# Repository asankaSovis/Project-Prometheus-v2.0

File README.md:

# 🔥 Project Prometheus v2.0

---

💸 Please consider donating on [Paypal](https://www.paypal.com/donate/?hosted_button_id=4EWXTWQ9FUFLA) to keep this project alive.

**Prometheus Fire Alarm System** is a fire alarm system and an extinguishing system that allows real-time monitoring via software. It can perform smart extinguishing on-site while simultaneously providing connectivity to multiple devices via the control panel. Prometheus is designed to be as simple and resilient as possible while making it safe to use and operate within a household.

**Prometheus 2.0** is the next generation of [Prometheus Fire Alarm System](https://github.com/asankaSovis/prometheus-fire-alarm); the future of household safety and monitoring. Developed on the nRF7002 platform, it brings all the features of v1.0 to the nRF platform along with additional features made possible by the nRF platform.

> 
> 3D view of the enclosure design

## 📜 License
> Project Prometheus v2.0 is licensed under the **GNU General Public License v3.0**.

Permissions of this strong copyleft license are conditioned on making available complete source code of licensed works and modifications, which include larger works using a licensed work, under the same license. Copyright and license notices must be preserved. Contributors provide an express grant of patent rights.

### Permissions
✔️ Commercial use | Modification | Distribution | Patent use | Private use

### Limitations
❌ Liability | Warranty

### Conditions
ℹ️ License and copyright notice | State changes | Disclose source | Same license 

Refer to the [License declaration](./LICENSE) for more details.

## 💾 Documentation
Please refer to the following links for different sections of documentation.

1. [Preface](./Documentation/Preface.md)
2. [Introduction](./Documentation/Introduction.md)
3. [Technical Specification](./Documentation/Technical_Specifications.md)
4. [Hardware Specification](./Documentation/Hardware_Specifications.md)
5. [Software Specification](./Documentation/Software_Specifications.md)
6. [Operational Details](./Documentation/Operational_Details.md)
7. [Project Management](./Documentation/Project_Management.md)
8. [Bill of Material](./Documentation/Bill_of_Material.md)
9. [References](./Documentation/References.md)
10. [Conclusion](./Documentation/Conclusion.md)

## 📊 Demonstration

> 
> Demonstration video of the final product

`© 2024 Asanka Sovis`

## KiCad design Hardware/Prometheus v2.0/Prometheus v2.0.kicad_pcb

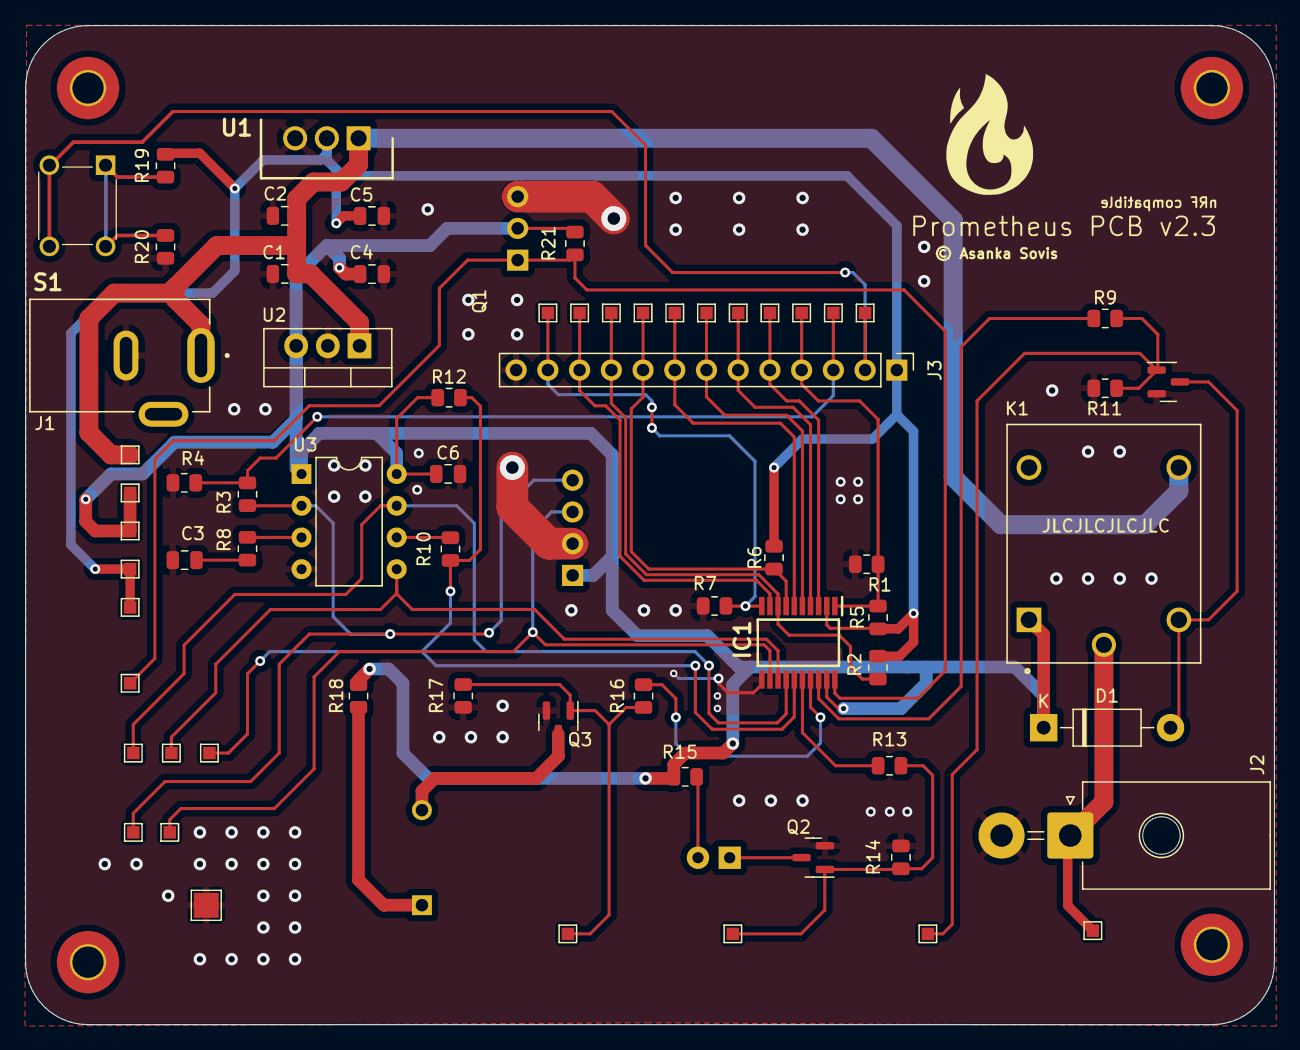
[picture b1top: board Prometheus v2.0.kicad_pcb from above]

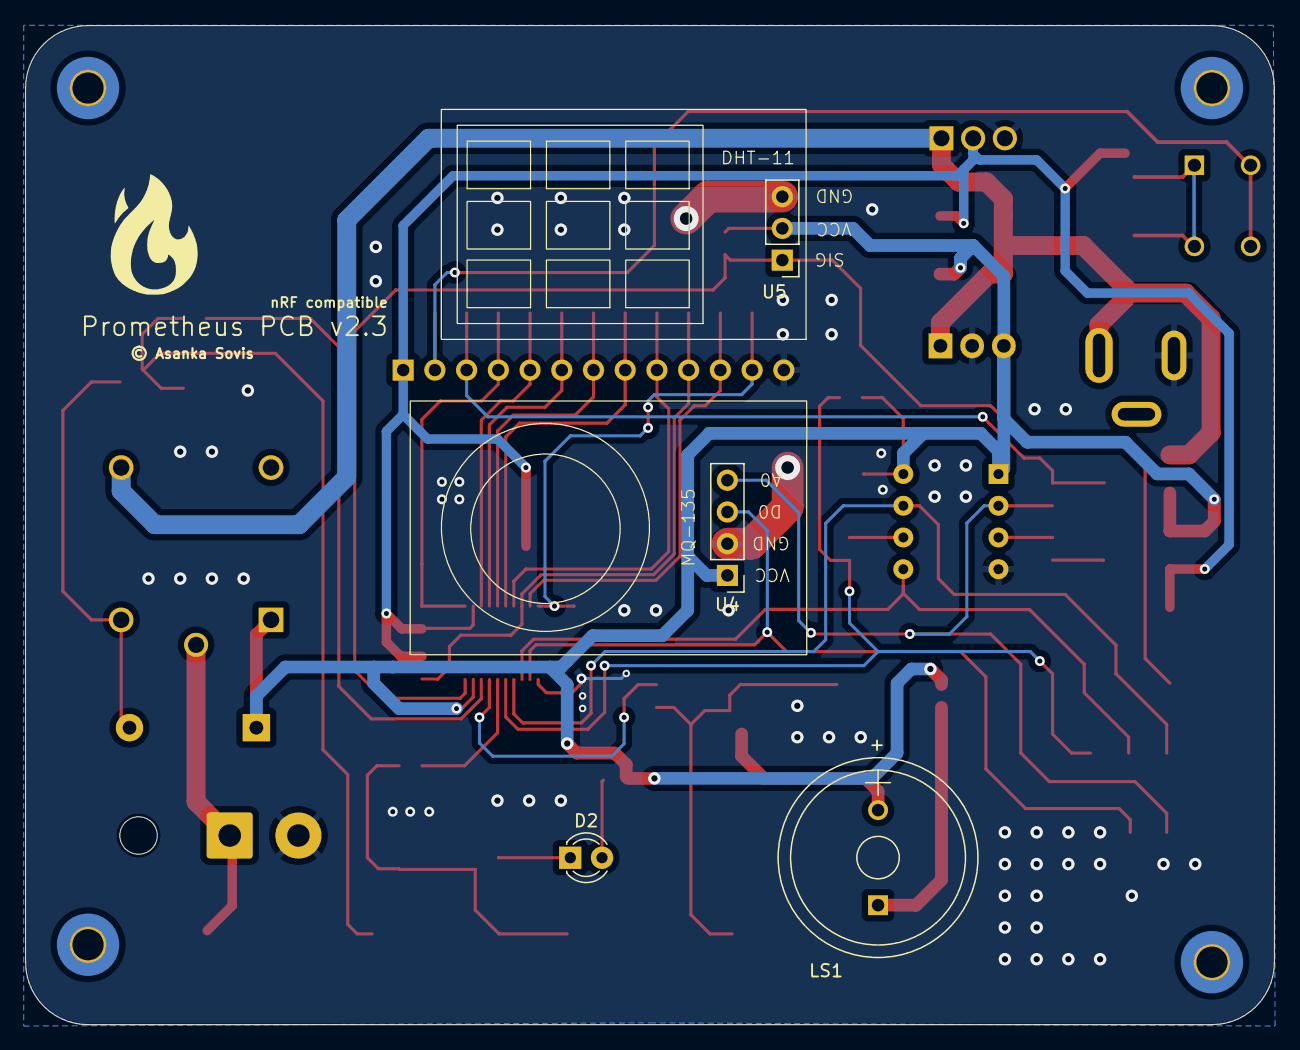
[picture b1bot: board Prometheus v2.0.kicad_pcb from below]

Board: 2 copper layers, 100.0 x 80.0 mm, 75 parts (4 on the bottom side), 37 nets.

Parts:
C1, C2, C4, C5: 10uF; C_0805_2012Metric
C3, C6: 0.1uF; C_0805_2012Metric
D1: 1N4001; D_DO-41_SOD81_P10.16mm_Horizontal
D2: LED; LED_D3.0mm_FlatTop
H1, H2, H3, H4: MountingHole; MountingHole_2.5mm_Pad_TopBottom
IC1: TXS0108EQPWRQ1; SOP65P640X120-20N
J1: DC-005-5A-2.0; XKB_DC-005-5A-2.0
J2: Conn_01x02_Socket; Molex_Mega-Fit_76825-0002_2x01_P5.70mm_Horizontal
J3: Conn_01x13_Pin; PinHeader_1x13_P2.54mm_Vertical
K1: SRD-05VDC-SL-C; RELAY_SRD-05VDC-SL-C
LS1: CPE-222H; MagneticBuzzer_StarMicronics_HMB-06_HMB-12
Q1, Q2, Q3: IRLML6246; SOT-23
R1, R2, R5, R6, R20: DNP; R_0805_2012Metric
R3, R7, R11, R12, R14, R17, R21: 10k; R_0805_2012Metric
R4: 20k; R_0805_2012Metric
R8: 2k; R_0805_2012Metric
R9, R10, R13, R16, R19: 100R; R_0805_2012Metric
R15, R18: 220R; R_0805_2012Metric
S1: DTS-62N-V; DTS62NV
TP1: 12V_TP; TestPoint_Pad_1.0x1.0mm
TP2: MQ_135_A_3V3_TP; TestPoint_Pad_1.0x1.0mm
TP3: VREF_A_TP; TestPoint_Pad_1.0x1.0mm
TP4: 5V_TP; TestPoint_Pad_1.0x1.0mm
TP5: 3V3_TP; TestPoint_Pad_1.0x1.0mm
TP6: LS_EN_TP; TestPoint_Pad_1.0x1.0mm
TP7: MQ_135_SCL_TP; TestPoint_Pad_1.0x1.0mm
TP8: MQ_135_CS_TP; TestPoint_Pad_1.0x1.0mm
TP9: VREF_B_TP; TestPoint_Pad_1.0x1.0mm
TP10: Solenoid_In_TP; TestPoint_Pad_1.0x1.0mm
TP11: MQ_135_SDA_TP; TestPoint_Pad_1.0x1.0mm
TP12: MQ_135_5V_TP; TestPoint_Pad_1.0x1.0mm
TP13: MQ_135_D_TP; TestPoint_Pad_1.0x1.0mm
TP14: Solenoid_Out_TP; TestPoint_Pad_1.0x1.0mm
TP15: LED_TP; TestPoint_Pad_1.0x1.0mm
TP16: Buzzer_TP; TestPoint_Pad_1.0x1.0mm
TP17: Solenoid_Control_3V3_TP; TestPoint_Pad_1.0x1.0mm
TP18: Indicator_Buzzer_3V3_TP; TestPoint_Pad_1.0x1.0mm
TP19: Indicator_LED_3V3_TP; TestPoint_Pad_1.0x1.0mm
TP20: DHT_11_3V3_TP; TestPoint_Pad_1.0x1.0mm
TP21: MQ_135_SDA_3V3_TP; TestPoint_Pad_1.0x1.0mm
TP22: MQ_135_SCL_3V3_TP; TestPoint_Pad_1.0x1.0mm
TP23: MQ_135_CS_3V3_TP; TestPoint_Pad_1.0x1.0mm
TP24: MQ_135_D_3V3_TP; TestPoint_Pad_1.0x1.0mm
TP25: GND_TP; TestPoint_Pad_2.0x2.0mm
TP26: DHT_11_TP; TestPoint_Pad_1.0x1.0mm
TP27: Reset_TP; TestPoint_Pad_1.0x1.0mm
U1: LMS1585ACT-3.3_NOPB; TO254P470X1028X1955-3P
U2: LM7805_TO220; TO-220-3_Vertical
U3: XD549; DIP-8_W7.62mm
U4: MQ-135
U5: DHT-11

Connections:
+3.3V: C5.1, IC1.2 (VCCA), J3.1, R2.1, R5.1, R6.1, R19.1, TP3.1, TP5.1, U1.2 (VO)
+5V: C4.1, C6.1, D1.1 (K), IC1.19 (VCCB), K1.A1, R12.1, R15.1, R18.1, R21.2, TP4.1, TP9.1, U2.3 (VO), U3.1 (REF+), U3.8 (VCC), U4.1 (VCC), U5.2 (VCC)
+12V: C1.1, C2.1, J1.1, K1.NO, TP1.1, U1.1 (VI), U2.1 (VI)
/DHT_11_3V3: IC1.1 (A1), J3.4, R1.1, R5.2, TP20.1
/DHT_11_5V: IC1.20 (B1), R21.1, TP26.1, U5.1 (SIG)
/Indicator_Buzzer: IC1.17 (B3), R16.1
/Indicator_Buzzer_3V3: IC1.4 (A3), J3.6, TP18.1
/Indicator_LED: IC1.16 (B4), R13.1
/Indicator_LED_3V3: IC1.5 (A4), J3.7, TP19.1
/LS_EN: IC1.10 (OE), J3.12, R7.1, TP6.1
/MQ_135_A: R3.1, TP12.1, U3.2 (A0), U4.4 (A0)
/MQ_135_A_3V3: J3.3, R3.2, R4.2, TP2.1
/MQ_135_CS: IC1.13 (B7), TP8.1, U3.5 (CS)
/MQ_135_CS_3V3: IC1.8 (A7), J3.10, R2.2, TP23.1
/MQ_135_D: IC1.12 (B8), TP13.1, U4.3 (D0)
/MQ_135_D_3V3: IC1.9 (A8), J3.11, TP24.1
/MQ_135_SCL: IC1.14 (B6), TP7.1, U3.7 (CLK)
/MQ_135_SCL_3V3: IC1.7 (A6), J3.9, R6.2, TP22.1
/MQ_135_SDA: IC1.15 (B5), R10.1, R12.2, TP11.1
/MQ_135_SDA_3V3: IC1.6 (A5), J3.8, TP21.1
/Solenoid_Control: IC1.18 (B2), R9.1
/Solenoid_Control_3V3: IC1.3 (A2), J3.5, TP17.1
/To_Reset: J3.2, S1.3 (N.O._1), S1.4 (N.O._2), TP27.1
/To_Solenoid: J2.1, K1.COM, TP14.1
GND: C1.2, C2.2, C3.1, C4.2, C5.2, C6.2, IC1.11 (GND), J1.2, J2.2, J3.13, Q1.2 (S), Q2.2 (S), Q3.2 (S), R1.2, R4.1, R7.2, R11.2, R14.2, R17.2, R20.1, TP25.1, U1.3 (GND), U2.2 (GND), U3.4 (GND), U4.2 (GND), U5.3 (GND)
unnamed: C3.2, R8.2
unnamed: D1.2 (A), K1.A2, Q1.3 (D)
unnamed: D2.2 (A), R15.2
unnamed: D2.1 (K), Q2.3 (D)
unnamed: LS1.1, R18.2
unnamed: Q1.1 (G), R9.2, R11.1, TP10.1
unnamed: Q2.1 (G), R13.2, R14.1, TP15.1
unnamed: LS1.2, Q3.3 (D)
unnamed: Q3.1 (G), R16.2, R17.1, TP16.1
unnamed: R19.2, R20.2, S1.1 (COM_1), S1.2 (COM_2)
unnamed: R8.1, U3.3 (REF-)
unnamed: R10.2, U3.6 (SDA)

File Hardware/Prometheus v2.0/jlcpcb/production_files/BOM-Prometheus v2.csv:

Comment,Designator,Footprint,LCSC
TXS0108EQPWRQ1,IC1,SOP65P640X120-20N,C1021790
20k,R4,R_0805_2012Metric,C114566
10k,"R11,R12,R14,R17,R21,R3,R7",R_0805_2012Metric,C138260
LMS1585ACT-3.3_NOPB,U1,TO254P470X1028X1955-3P,C140341
1N4001,D1,D_DO-41_SOD81_P10.16mm_Horizontal,C145491
DTS-62N-V,S1,DTS62NV,C224975
220R,"R15,R18",R_0805_2012Metric,C340559
DC-005-5A-2.0,J1,XKB_DC-005-5A-2.0,C381116
2k,R8,R_0805_2012Metric,C413188
0.1uF,"C3,C6",C_0805_2012Metric,C519930
LM7805_TO220,U2,TO-220-3_Vertical,C5444281
XD549,U3,DIP-8_W7.62mm,C707061
100R,"R10,R13,R16,R19,R9",R_0805_2012Metric,C728002
IRLML6246,"Q1,Q2,Q3",SOT-23,C82053
10uF,"C1,C2,C4,C5",C_0805_2012Metric,C89832
CPE-222H,LS1,MagneticBuzzer_StarMicronics_HMB-06_HMB-12,C96095
SRD-05VDC-SL-C,K1,RELAY_SRD-05VDC-SL-C,C99666
LED,D2,LED_D3.0mm_FlatTop,C99758
MQ_135_D_TP,TP13,TestPoint_Pad_1.0x1.0mm,
LED_TP,TP15,TestPoint_Pad_1.0x1.0mm,
MountingHole,H4,MountingHole_2.5mm_Pad_TopBottom,
MQ_135_5V_TP,TP12,TestPoint_Pad_1.0x1.0mm,
VREF_A_TP,TP3,TestPoint_Pad_1.0x1.0mm,
DHT_11_3V3_TP,TP20,TestPoint_Pad_1.0x1.0mm,
DNP,R20,R_0805_2012Metric,
GND_TP,TP25,TestPoint_Pad_2.0x2.0mm,
DNP,R2,R_0805_2012Metric,
MQ_135_D_3V3_TP,TP24,TestPoint_Pad_1.0x1.0mm,
MQ_135_SCL_TP,TP7,TestPoint_Pad_1.0x1.0mm,
Indicator_LED_3V3_TP,TP19,TestPoint_Pad_1.0x1.0mm,
LS_EN_TP,TP6,TestPoint_Pad_1.0x1.0mm,
DNP,R1,R_0805_2012Metric,
12V_TP,TP1,TestPoint_Pad_1.0x1.0mm,
Solenoid_Control_3V3_TP,TP17,TestPoint_Pad_1.0x1.0mm,
Solenoid_Out_TP,TP14,TestPoint_Pad_1.0x1.0mm,
Buzzer_TP,TP16,TestPoint_Pad_1.0x1.0mm,
MQ_135_SDA_TP,TP11,TestPoint_Pad_1.0x1.0mm,
5V_TP,TP4,TestPoint_Pad_1.0x1.0mm,
Reset_TP,TP27,TestPoint_Pad_1.0x1.0mm,
MQ_135_SDA_3V3_TP,TP21,TestPoint_Pad_1.0x1.0mm,
MountingHole,H3,MountingHole_2.5mm_Pad_TopBottom,
Solenoid_In_TP,TP10,TestPoint_Pad_1.0x1.0mm,
DHT_11_TP,TP26,TestPoint_Pad_1.0x1.0mm,
DNP,R6,R_0805_2012Metric,
Conn_01x13_Pin,J3,PinHeader_1x13_P2.54mm_Vertical,
MountingHole,H2,MountingHole_2.5mm_Pad_TopBottom,
Conn_01x02_Socket,J2,Molex_Mega-Fit_76825-0002_2x01_P5.70mm_Horizontal,
MountingHole,H1,MountingHole_2.5mm_Pad_TopBottom,
Indicator_Buzzer_3V3_TP,TP18,TestPoint_Pad_1.0x1.0mm,
MQ_135_SCL_3V3_TP,TP22,TestPoint_Pad_1.0x1.0mm,
DNP,R5,R_0805_2012Metric,
MQ_135_CS_3V3_TP,TP23,TestPoint_Pad_1.0x1.0mm,
MQ_135_A_3V3_TP,TP2,TestPoint_Pad_1.0x1.0mm,
3V3_TP,TP5,TestPoint_Pad_1.0x1.0mm,
MQ_135_CS_TP,TP8,TestPoint_Pad_1.0x1.0mm,
VREF_B_TP,TP9,TestPoint_Pad_1.0x1.0mm,
DHT-11,U5,DHT-11,
MQ-135,U4,MQ-135,

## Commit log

2023-11-04 Phase 01 - v1.0
    - Power circuitry, reset, indicators and relay
2023-11-04 v1.0 - Phase 2
    - Completed the complete schematic
2023-11-10 v2.1
    - First design completion
2023-11-23 v2.2
2024-01-13 Finalized Hardware
    - Finalized hardware that was printed.
2024-01-13 Finalized Firmware for v2.0
    - Finalized basic firmware for nRF7002
2024-01-14 Bug Fixes, Documentation and Feature
    - Bug fixes for initialization check
    - Added builtin indicator to indicate device status
    - Documentation
2024-01-14 Updated BOM
    - Generated HTML BOM for the project
2024-01-15 Added Documentation files and Enclosure View
    - Added documentation files
    - Added enclosure step file and related images
2024-01-15 Fixed Technical Issues and Extra Figures
    - Fixed technical issues in documentation
    - Added more figures
2024-01-15 Updated Documentation
    - Updated Documentation
2024-01-15 Initial Setup of Matter
    - Initial Setup of Matter
2024-04-19 Added Exclude File to Git Attribute file
    .gitattribute file updated to ignore Hardware directory to ignore HTML entries in the BOM. This eliminates the issue of primary language being detected as HTML.
2024-05-25 Updated gitattribute file.
2024-05-25 Zipped hardware design

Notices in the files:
Hardware/Prometheus v2.0/Prometheus v2.0.kicad_pcb:
© Asanka Sovis
